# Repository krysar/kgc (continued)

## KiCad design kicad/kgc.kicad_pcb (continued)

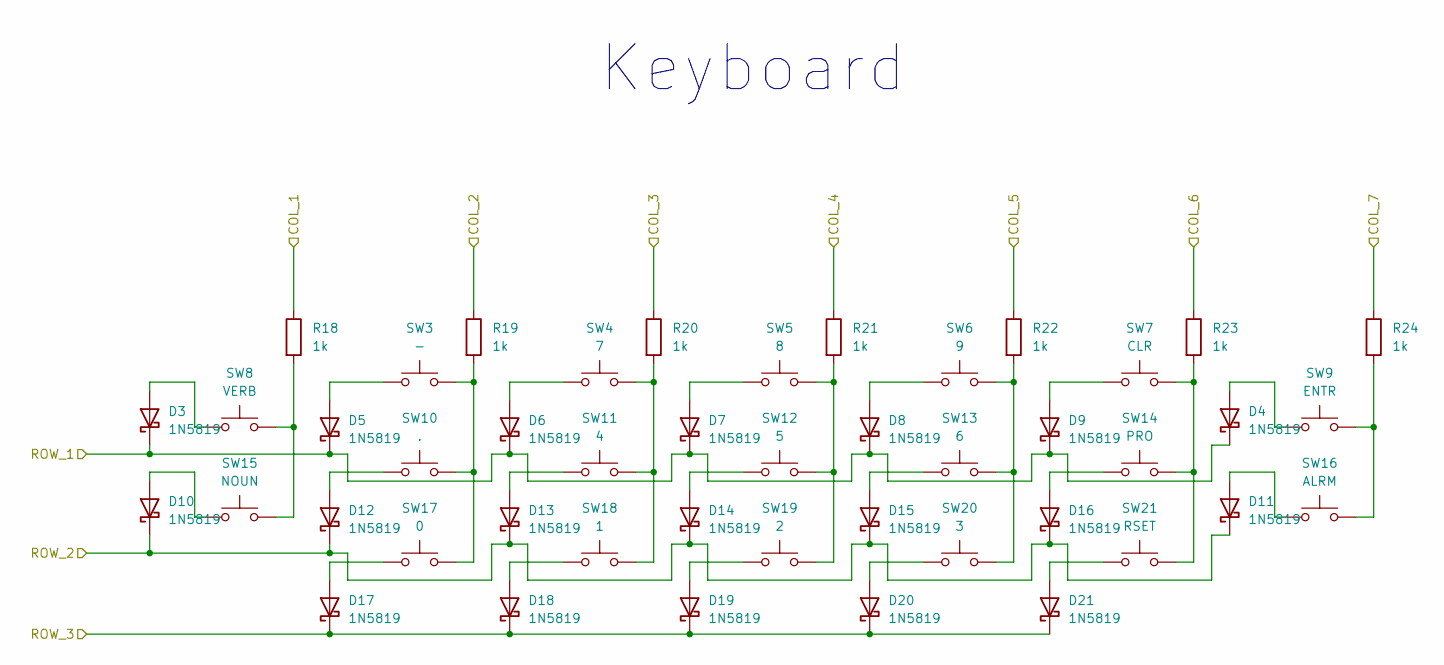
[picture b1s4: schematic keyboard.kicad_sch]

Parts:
D3, D4, D5, D6, D7, D8, D9, D10, D11, D12, D13, D14, D15, D16, D17, D18, D19, D20, D21: 1N5819; D_DO-41_SOD81_P7.62mm_Horizontal
R18, R19, R20, R21, R22, R23, R24: 1k; R_0603_1608Metric_Pad0.98x0.95mm_HandSolder
SW3: -; SW_Cherry_MX_1.00u_PCB
SW4: 7; SW_Cherry_MX_1.00u_PCB
SW5: 8; SW_Cherry_MX_1.00u_PCB
SW6: 9; SW_Cherry_MX_1.00u_PCB
SW7: CLR; SW_Cherry_MX_1.00u_PCB
SW8: VERB; SW_Cherry_MX_1.00u_PCB
SW9: ENTR; SW_Cherry_MX_1.00u_PCB
SW10: .; SW_Cherry_MX_1.00u_PCB
SW11: 4; SW_Cherry_MX_1.00u_PCB
SW12: 5; SW_Cherry_MX_1.00u_PCB
SW13: 6; SW_Cherry_MX_1.00u_PCB
SW14: PRO; SW_Cherry_MX_1.00u_PCB
SW15: NOUN; SW_Cherry_MX_1.00u_PCB
SW16: ALRM; SW_Cherry_MX_1.00u_PCB
SW17: 0; SW_Cherry_MX_1.00u_PCB
SW18: 1; SW_Cherry_MX_1.00u_PCB
SW19: 2; SW_Cherry_MX_1.00u_PCB
SW20: 3; SW_Cherry_MX_1.00u_PCB
SW21: RSET; SW_Cherry_MX_1.00u_PCB

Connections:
/KBD_COL_1: R18.1; also elsewhere on the board
/KBD_COL_2: R19.1; also elsewhere on the board
/KBD_COL_3: R20.1; also elsewhere on the board
/KBD_COL_4: R21.1; also elsewhere on the board
/KBD_COL_5: R22.1; also elsewhere on the board
/KBD_COL_6: R23.1; also elsewhere on the board
/KBD_COL_7: R24.1; also elsewhere on the board
/KBD_ROW_1: D3.1 (K), D4.1 (K), D5.1 (K), D6.1 (K), D7.1 (K), D8.1 (K), D9.1 (K); also elsewhere on the board
/KBD_ROW_2: D10.1 (K), D11.1 (K), D12.1 (K), D13.1 (K), D14.1 (K), D15.1 (K), D16.1 (K); also elsewhere on the board
/KBD_ROW_3: D17.1 (K), D18.1 (K), D19.1 (K), D20.1 (K), D21.1 (K); also elsewhere on the board
unnamed: D3.2 (A), SW8.1
unnamed: D4.2 (A), SW9.1
unnamed: D5.2 (A), SW3.1
unnamed: D6.2 (A), SW4.1
unnamed: D7.2 (A), SW5.1
unnamed: D8.2 (A), SW6.1
unnamed: D9.2 (A), SW7.1
unnamed: D10.2 (A), SW15.1
unnamed: D11.2 (A), SW16.1
unnamed: D12.2 (A), SW10.1
unnamed: D13.2 (A), SW11.1
unnamed: D14.2 (A), SW12.1
unnamed: D15.2 (A), SW13.1
unnamed: D16.2 (A), SW14.1
unnamed: D17.2 (A), SW17.1
unnamed: D18.2 (A), SW18.1
unnamed: D19.2 (A), SW19.1
unnamed: D20.2 (A), SW20.1
unnamed: D21.2 (A), SW21.1
unnamed: R18.2, SW8.2, SW15.2
unnamed: R19.2, SW3.2, SW10.2, SW17.2
unnamed: R20.2, SW4.2, SW11.2, SW18.2
unnamed: R21.2, SW5.2, SW12.2, SW19.2
unnamed: R22.2, SW6.2, SW13.2, SW20.2
unnamed: R23.2, SW7.2, SW14.2, SW21.2
unnamed: R24.2, SW9.2, SW16.2

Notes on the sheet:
Keyboard

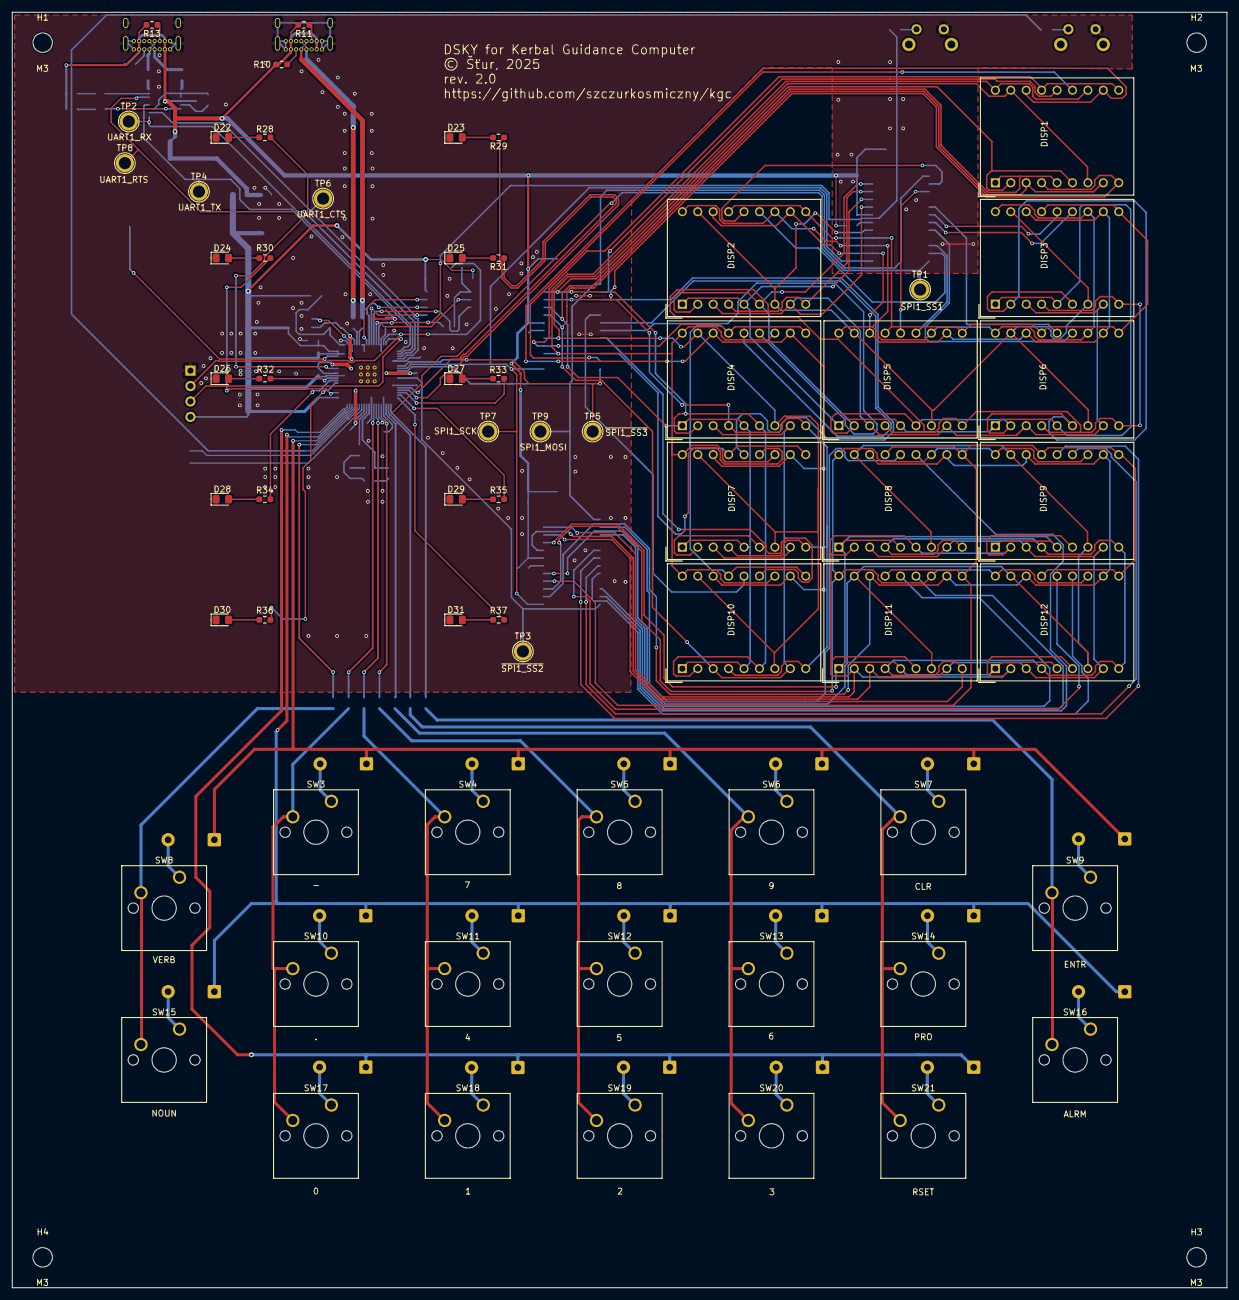
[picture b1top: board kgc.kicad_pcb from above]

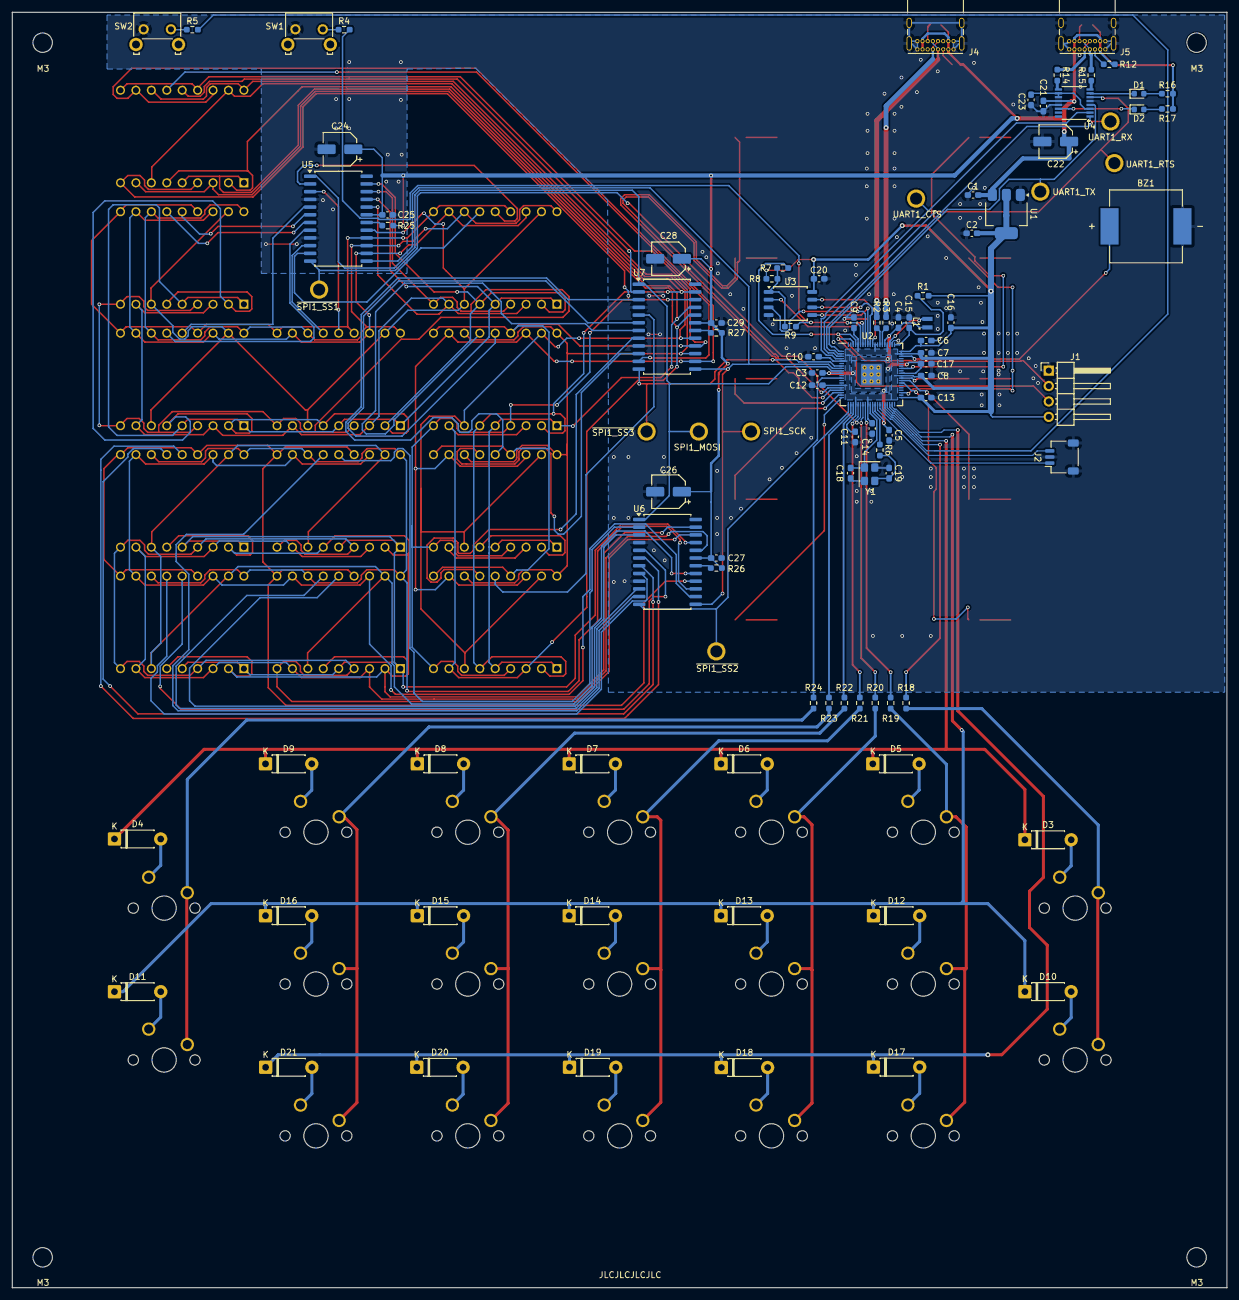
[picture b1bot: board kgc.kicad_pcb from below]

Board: 2 copper layers, 200.0 x 210.0 mm, 157 parts (90 on the bottom side), 157 nets.

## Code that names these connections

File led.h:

#ifndef KGC_LED_H
#define KGC_LED_H

#define LED_CNT 10
#define LED_CON 2
#define LED_FLD 3
#define LED_ELC 7
#define LED_MOP 9
#define LED_LFO 8
#define LED_OTR 10
#define LED_SAS 6
#define LED_RCS 11
#define LED_GEA 4
#define LED_BRK 12
#define BUZZ    14

#define LED_STAT_CON 0
#define LED_STAT_FLD 1
#define LED_STAT_ELC 2
#define LED_STAT_MOP 3
#define LED_STAT_LFO 4
#define LED_STAT_OTR 5
#define LED_STAT_SAS 6
#define LED_STAT_RCS 7
#define LED_STAT_GEA 8
#define LED_STAT_BRK 9
#define LED_STAT_BUZZ 10
#define LED_STAT_DISP1 11

#include "connection.h"

extern bool led_stat[12];
extern bool blink_stat;
extern struct repeating_timer led_blink_tmr;

void led_init();
void led_update(KSP_DATA ksp_in);
bool led_blinker(__unused struct repeating_timer *t);


#endif //KGC_LED_H

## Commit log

2022-02-14 Added schematic and PCB files
2022-02-27 -Comments improve -New (but already deprecated :D) method section and command combining
2022-03-06 New program switching system, support for LED indicators and buzzer, clear_display now clears individual displays, electrical schematic improvements
    kgc.c:
    - New macros for LEDs and buzzer GPIO pins.
    - New function led_init for initializing LEDs and buzzer GPIOs.
    - Section and command system was replaced by verb and nouns (yes, I robed it from AGC). Verbs are commands, nouns are relatively independent parameters for verbs (mostly kind of displayed data) . Ver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
    - Verbs list:
    - 00 for no operation
2025-06-01 Major updates
    Updated SDK version (2.1.1)
    kgc.c:
    - Almost everything was deleted - code was trash and I forgot how it works.
    - In main function is for now only some testing code.
    - New welcome message after device starts. xD
    max7219.(h/c):
2025-06-01 License file correction
2025-06-02 Added communication with KSP :poggies:
    New (.c/.h) files for UART communication with PC, new Python program for communication between KSP and KGC.
    KGC is now able to show altitude, apoapsis and periapsis through Verb 1, Noun 1.
    Still pretty buggy, Python program crashes when there isn't any active vessel. :)
2025-06-02 Added KiCad project files
2025-06-03 Fixed python program crashing when game scene isn't flight, code cleanup
2025-06-03 New handshake, kgc_pc is now kgc_server, several smaller changes
    kgc_server.py, kgc.c:
    - Handshake implementated (now KGC must send message to server and server must answer on the beggining of communication)
    - New verb 99 for output testing:
    - Noun 01 for displays test
    - Noun 02 for test of communication with server (KGC is receiving 1 incrementing number from server)
    connection.(h/c):
2025-06-03 Updated CMakeList for led.(h/c)
2025-06-03 README update
2025-06-04 Added several new Nouns for Verb 1
2025-06-04 Defined format of UART string
    connection.(h/c):
    - New struct for data from server
    - New uart_data_decoder() function for decoding UART input string
    - kgc.c:
    - String decoding delecated to uart_data_decoder() function.
    - Switch for Verb 1's Nouns replaced by simple if - else
2025-06-04 Support for FLD, SAS, RCS, GEA and BRK LEDs, info about game pause added to UART string
    connection.(h/c):
    - Sending data period now defined by macro and reduced to 250 ms
    - Added support for information about paused game
    led.(h/c):
    - New functions for update LEDs state from KSP_DATA struct
    kgc_server.py:
2025-06-04 New Verbs and Nouns, README updated
2025-06-04 Typo corrected
2025-06-05 New nouns for monitoring resources, blinking LEDs when resources are running out
2025-06-05 New Verbs/Nouns for take off and landing
2025-06-06 Several updates
    - Support for displaying float numbers
    - Several Verbs/Nouns displayed as floats
    - Reduced SPI baudrate
    - Changed time format
    - Fixed server crashing when V:1;N:9/10 and no SoI change
    - New verb 4 for next maneuver informations
2025-06-06 Fixed bug in V:5;N:1
2025-06-06 Small improvements
2025-06-08 Support for entering float numbers from the keypad
2025-06-08 Added check for maximum length of inserted string
2025-06-09 Improved keypad number entering, smaller improvements
2025-06-09 New Verb 12 for basic vessel control
2025-06-10 Preparation for ascent autopilot
2025-06-11 Verb 13 - Ascent autopilot
2025-06-11 Updated docs
2025-06-11 Higher SPI baudrate, Verb & Noun is now blinking when DSKY waits for confirm
2025-06-13 README update, typos correction
2025-06-15 Node creation, small fixes
2025-06-27 New hardware revision
    - Created new PCB
    - KiCad project updated
2025-06-27 Created box and keycap
    Created new keycaps and box for PCB
